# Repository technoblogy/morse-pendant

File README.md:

# Morse Code Message Pendant
A pendant that transmits a secret message in morse code by flashing an LED.

See <http://www.technoblogy.com/show?3TAC>.

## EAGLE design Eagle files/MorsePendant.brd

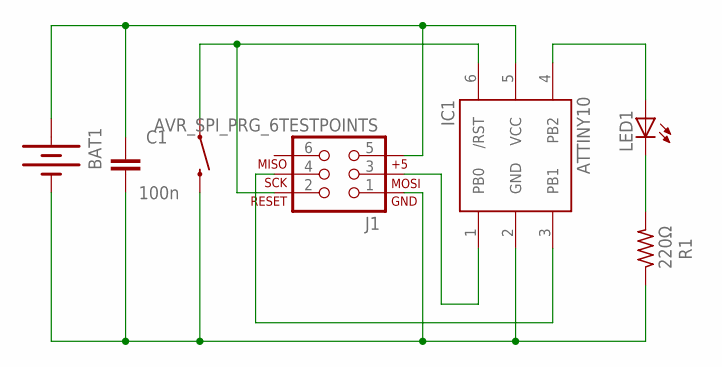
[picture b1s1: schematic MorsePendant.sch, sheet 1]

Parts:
BAT1: BATTERY12MM; BATTCON_12MM
C1: 100n; 0603-CAP
IC1: ATTINY10; SOT23-6
J1: AVR_SPI_PRG_6TESTPOINTS; 2X3_TEST_POINTS
LED1: LEDCHIPLED_0805; CHIPLED_0805
R1: 220Ω; R0805
S2: SWITCH-MOMENTARY-2SMD; TACTILE-SWITCH-SMD

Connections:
unnamed: BAT1.PWR@1 (+), C1.1, IC1.5 (VCC), J1.5
unnamed: IC1.6 (/RST), J1.2, S2.1
unnamed: IC1.4 (PB2), LED1.A
unnamed: LED1.C, R1.2
unnamed: IC1.1 (PB0), J1.3
unnamed: BAT1.GND (-), C1.2, IC1.2 (GND), J1.1, R1.1, S2.3 (2)
unnamed: IC1.3 (PB1), J1.4

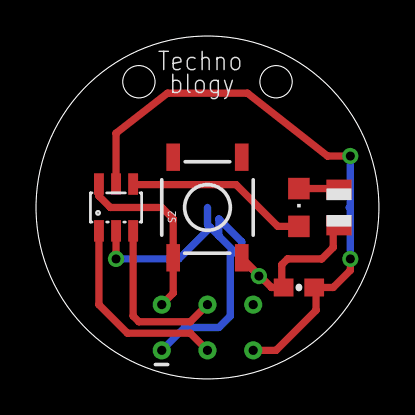
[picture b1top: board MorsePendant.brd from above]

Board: 2 copper layers, 19.1 x 19.1 mm, 7 parts (1 on the bottom side), 7 nets.

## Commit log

2022-02-14 Version 1 - 14th February 2022

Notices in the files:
parts and their libraries:
SparkFun-Capacitors: Licensing: CC v3.0 Share-Alike You are welcome to use this library for commercial purposes.
SparkFun-Electromechanical: Licensing: Creative Commons ShareAlike 4.0 International - https://creativecommons.org/licenses/by-sa/4.0
